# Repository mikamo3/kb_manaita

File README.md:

# kb_manaita
Self made 40% keyboard

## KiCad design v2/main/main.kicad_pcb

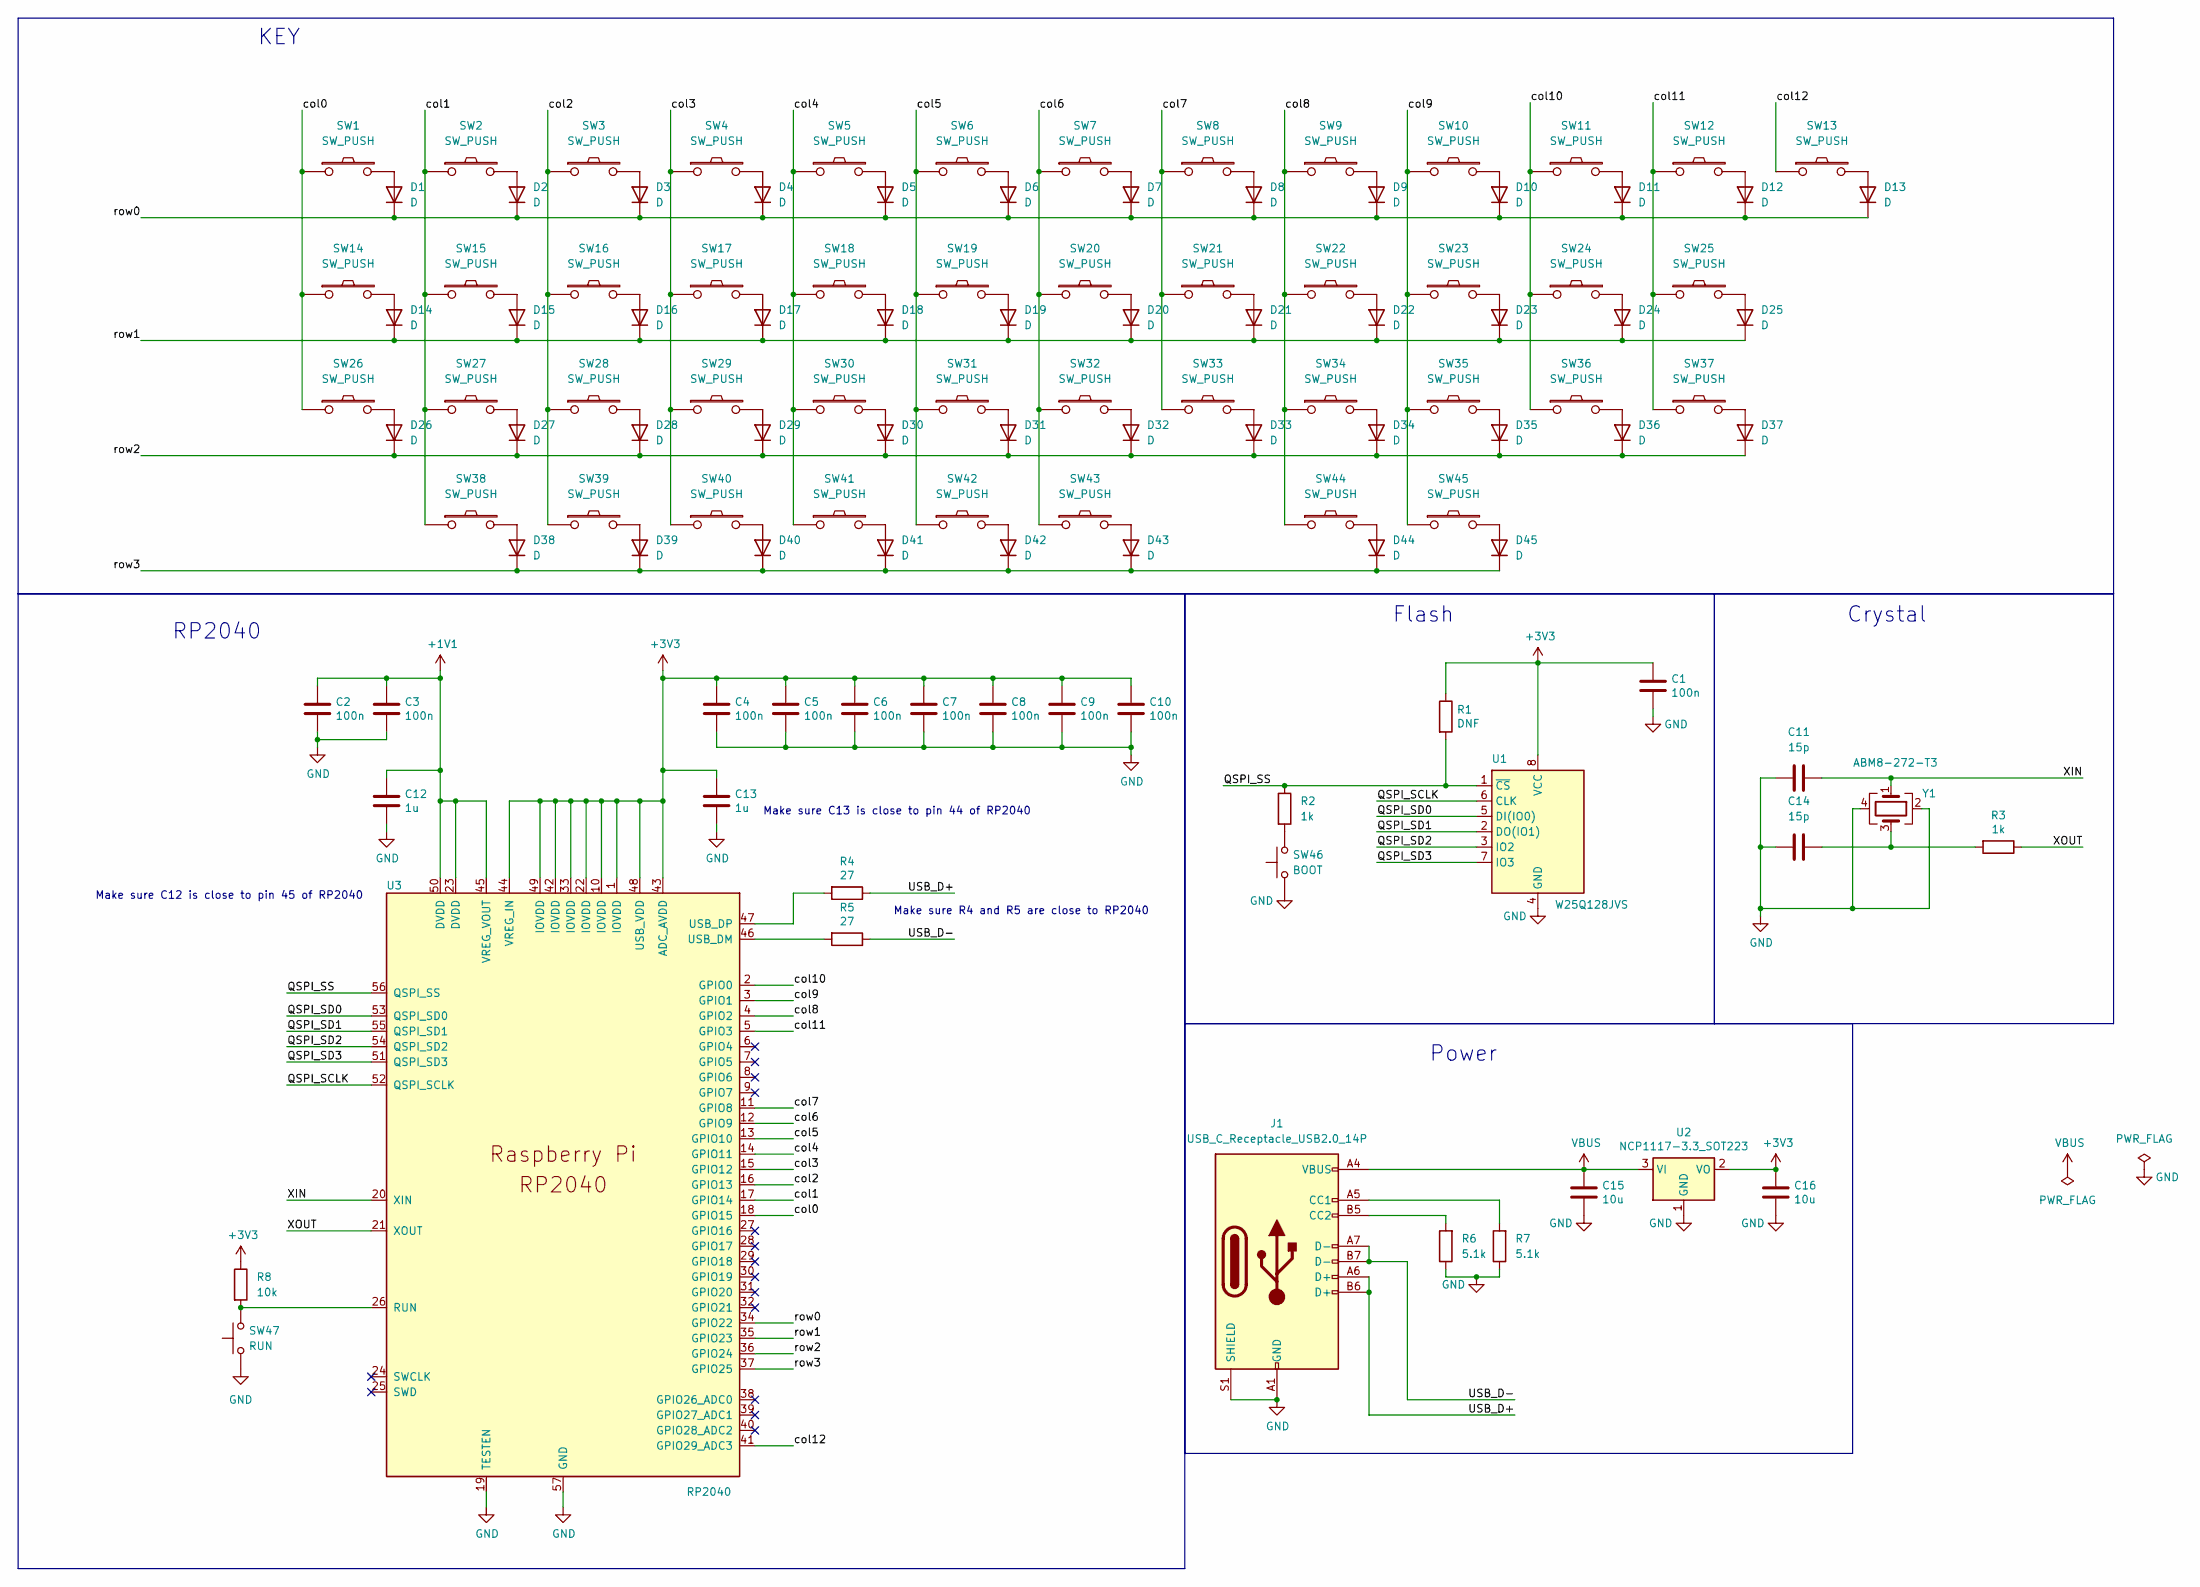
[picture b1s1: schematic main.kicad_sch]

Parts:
C1, C2, C3, C4, C5, C6, C7, C8, C9, C10: 100n; C_0402_1005Metric; LCSC C307331
C11, C14: 15p; C_0603_1608Metric; LCSC C1548
C12, C13: 1u; C_0402_1005Metric; LCSC C52923
C15, C16: 10u; C_0805_2012Metric; LCSC C15850
D1, D2, D3, D4, D5, D6, D7, D8, D9, D10, D11, D12, D13, D14, D15, D16, D17, D18, D19, D20, D21, D22, D23, D24, D25, D26, D27, D28, D29, D30, D31, D32, D33, D34, D35, D36, D37, D38, D39, D40, D41, D42, D43, D44, D45: D; Diode_SOD123; LCSC C8598
J1: USB_C_Receptacle_USB2.0_14P; USB_C_Receptacle_Palconn_UTC16-G; LCSC C2988369
R1: DNF; R_0402_1005Metric
R2, R3: 1k; R_0402_1005Metric; LCSC C11702
R4, R5: 27; R_0603_1608Metric; LCSC C25190
R6, R7: 5.1k; R_0402_1005Metric; LCSC C25905
R8: 10k; R_0402_1005Metric; LCSC C25744
SW1, SW2, SW3, SW4, SW5, SW6, SW7, SW8, SW9, SW10, SW11, SW12, SW13, SW15, SW16, SW17, SW18, SW19, SW20, SW21, SW22, SW23, SW24, SW27, SW28, SW29, SW30, SW31, SW32, SW33, SW34, SW35, SW36, SW41, SW42: SW_PUSH; SW_CherryMX_Hotswap_1.00u
SW14, SW37, SW38, SW39, SW40, SW43, SW44, SW45: SW_PUSH; SW_CherryMX_Hotswap_1.25u
SW25, SW26: SW_PUSH; SW_CherryMX_Hotswap_1.75u
SW46: BOOT; Tact_Switch_5.1_5.1mm_SMD; LCSC C318884
SW47: RUN; Tact_Switch_5.1_5.1mm_SMD; LCSC C318884
U1: W25Q128JVS; SOIC-8_5.23x5.23mm_P1.27mm; LCSC C97521
U2: NCP1117-3.3_SOT223; SOT-223-3_TabPin2; LCSC C6186
U3: RP2040; RP2040-QFN-56; LCSC C2040
Y1: ABM8-272-T3; Crystal_SMD_3225-4Pin_3.2x2.5mm; LCSC C9002

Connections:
+1V1: C2.1, C3.1, C12.1, U3.23 (DVDD), U3.45 (VREG_VOUT), U3.50 (DVDD)
+3V3: C1.1, C4.1, C5.1, C6.1, C7.1, C8.1, C9.1, C10.1, C13.1, C16.1, R1.1, R8.1, U1.8 (VCC), U2.2 (VO), U3.1 (IOVDD), U3.10 (IOVDD), U3.22 (IOVDD), U3.33 (IOVDD), U3.42 (IOVDD), U3.43 (ADC_AVDD), U3.44 (VREG_IN), U3.48 (USB_VDD), U3.49 (IOVDD)
/QSPI_SCLK: U1.6 (CLK), U3.52 (QSPI_SCLK)
/QSPI_SD0: U1.5 (DI(IO0)), U3.53 (QSPI_SD0)
/QSPI_SD1: U1.2 (DO(IO1)), U3.55 (QSPI_SD1)
/QSPI_SD2: U1.3 (IO2), U3.54 (QSPI_SD2)
/QSPI_SD3: U1.7 (IO3), U3.51 (QSPI_SD3)
/QSPI_SS: R1.2, R2.1, U1.1 (~CS), U3.56 (QSPI_SS)
/USB_D+: J1.A6 (D+), J1.B6 (D+), R4.1
/USB_D-: J1.A7 (D-), J1.B7 (D-), R5.1
/XIN: C11.2, U3.20 (XIN), Y1.1
/XOUT: R3.1, U3.21 (XOUT)
/col0: SW1.1, SW14.1, SW26.1, U3.18 (GPIO15)
/col1: SW2.1, SW15.1, SW27.1, SW38.1, U3.17 (GPIO14)
/col2: SW3.1, SW16.1, SW28.1, SW39.1, U3.16 (GPIO13)
/col3: SW4.1, SW17.1, SW29.1, SW40.1, U3.15 (GPIO12)
/col4: SW5.1, SW18.1, SW30.1, SW41.1, U3.14 (GPIO11)
/col5: SW6.1, SW19.1, SW31.1, SW42.1, U3.13 (GPIO10)
/col6: SW7.1, SW20.1, SW32.1, SW43.1, U3.12 (GPIO9)
/col7: SW8.1, SW21.1, SW33.1, U3.11 (GPIO8)
/col8: SW9.1, SW22.1, SW34.1, SW44.1, U3.4 (GPIO2)
/col9: SW10.1, SW23.1, SW35.1, SW45.1, U3.3 (GPIO1)
/col10: SW11.1, SW24.1, SW36.1, U3.2 (GPIO0)
/col11: SW12.1, SW25.1, SW37.1, U3.5 (GPIO3)
/col12: SW13.1, U3.41 (GPIO29_ADC3)
/row0: D1.1 (K), D2.1 (K), D3.1 (K), D4.1 (K), D5.1 (K), D6.1 (K), D7.1 (K), D8.1 (K), D9.1 (K), D10.1 (K), D11.1 (K), D12.1 (K), D13.1 (K), U3.34 (GPIO22)
/row1: D14.1 (K), D15.1 (K), D16.1 (K), D17.1 (K), D18.1 (K), D19.1 (K), D20.1 (K), D21.1 (K), D22.1 (K), D23.1 (K), D24.1 (K), D25.1 (K), U3.35 (GPIO23)
/row2: D26.1 (K), D27.1 (K), D28.1 (K), D29.1 (K), D30.1 (K), D31.1 (K), D32.1 (K), D33.1 (K), D34.1 (K), D35.1 (K), D36.1 (K), D37.1 (K), U3.36 (GPIO24)
/row3: D38.1 (K), D39.1 (K), D40.1 (K), D41.1 (K), D42.1 (K), D43.1 (K), D44.1 (K), D45.1 (K), U3.37 (GPIO25)
GND: C1.2, C2.2, C3.2, C4.2, C5.2, C6.2, C7.2, C8.2, C9.2, C10.2, C11.1, C12.2, C13.2, C14.1, C15.2, C16.2, J1.A1 (GND), J1.A12 (GND), J1.B1 (GND), J1.B12 (GND), J1.S1 (SHIELD), R6.1, R7.1, SW46.1, SW46.2, SW47.1, SW47.2, U1.4 (GND), U2.1 (GND), U3.19 (TESTEN), U3.57 (GND), Y1.2, Y1.4
unnamed: C14.2, R3.2, Y1.3
unnamed: D1.2 (A), SW1.2
unnamed: D2.2 (A), SW2.2
unnamed: D3.2 (A), SW3.2
unnamed: D4.2 (A), SW4.2
unnamed: D5.2 (A), SW5.2
unnamed: D6.2 (A), SW6.2
unnamed: D7.2 (A), SW7.2
unnamed: D8.2 (A), SW8.2
unnamed: D9.2 (A), SW9.2
unnamed: D10.2 (A), SW10.2
unnamed: D11.2 (A), SW11.2
unnamed: D12.2 (A), SW12.2
unnamed: D13.2 (A), SW13.2
unnamed: D14.2 (A), SW14.2
unnamed: D15.2 (A), SW15.2
unnamed: D16.2 (A), SW16.2
unnamed: D17.2 (A), SW17.2
unnamed: D18.2 (A), SW18.2
unnamed: D19.2 (A), SW19.2
unnamed: D20.2 (A), SW20.2
unnamed: D21.2 (A), SW21.2
unnamed: D22.2 (A), SW22.2
unnamed: D23.2 (A), SW23.2
unnamed: D24.2 (A), SW24.2
unnamed: D25.2 (A), SW25.2
unnamed: D26.2 (A), SW26.2
unnamed: D27.2 (A), SW27.2
unnamed: D28.2 (A), SW28.2
unnamed: D29.2 (A), SW29.2
unnamed: D30.2 (A), SW30.2
unnamed: D31.2 (A), SW31.2
unnamed: D32.2 (A), SW32.2
unnamed: D33.2 (A), SW33.2
unnamed: D34.2 (A), SW34.2
unnamed: D35.2 (A), SW35.2
unnamed: D36.2 (A), SW36.2
unnamed: D37.2 (A), SW37.2
unnamed: D38.2 (A), SW38.2
unnamed: D39.2 (A), SW39.2
unnamed: D40.2 (A), SW40.2
unnamed: D41.2 (A), SW41.2
unnamed: D42.2 (A), SW42.2
unnamed: D43.2 (A), SW43.2
unnamed: D44.2 (A), SW44.2
unnamed: D45.2 (A), SW45.2
unnamed: J1.A5 (CC1), R7.2
unnamed: J1.B5 (CC2), R6.2
unnamed: R2.2, SW46.3, SW46.4
unnamed: R8.2, SW47.3, SW47.4, U3.26 (RUN)
unnamed: R5.2, U3.46 (USB_DM)
unnamed: R4.2, U3.47 (USB_DP)
VBUS: C15.1, J1.A4 (VBUS), J1.A9 (VBUS), J1.B4 (VBUS), J1.B9 (VBUS), U2.3 (VI)

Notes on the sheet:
KEY
RP2040
Make sure R4 and R5 are close to RP2040
Power
Flash
Crystal
Make sure C12 is close to pin 45 of RP2040
Make sure C13 is close to pin 44 of RP2040

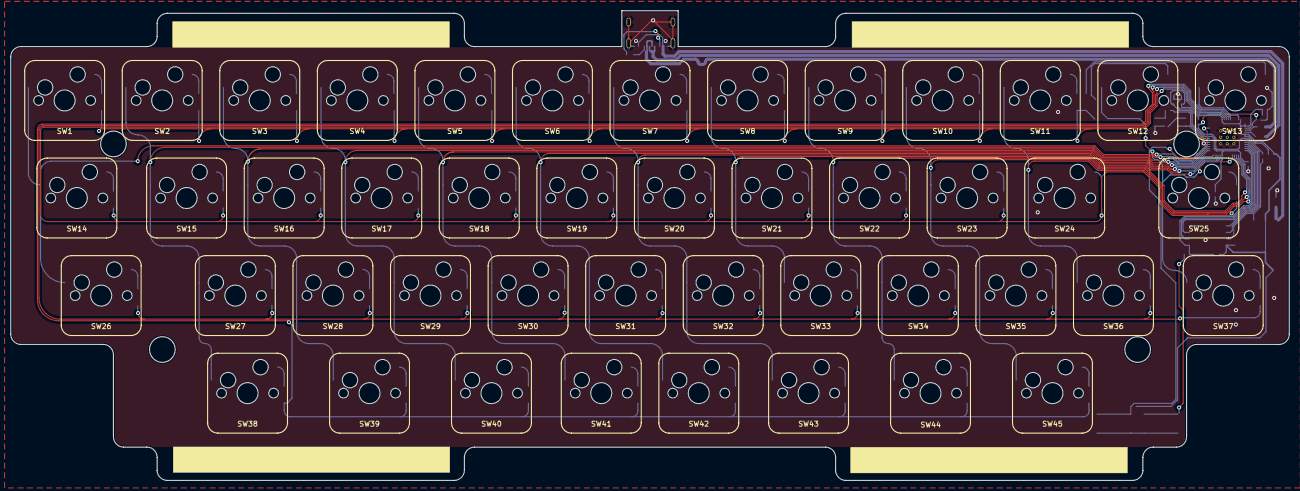
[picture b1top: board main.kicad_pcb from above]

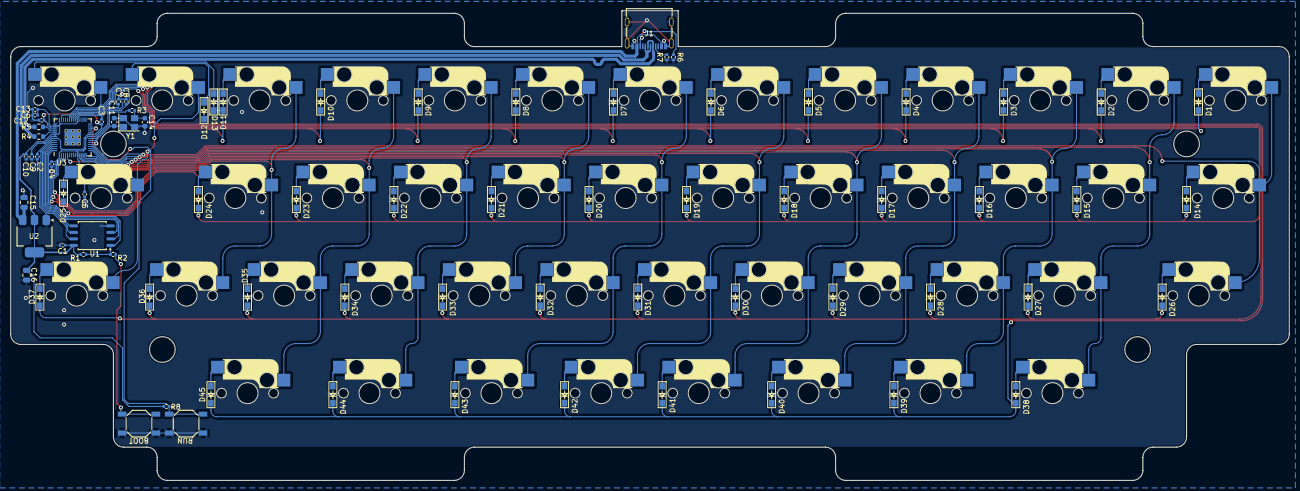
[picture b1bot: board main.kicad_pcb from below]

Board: 2 copper layers, 249.6 x 91.7 mm, 121 parts (76 on the bottom side), 83 nets.

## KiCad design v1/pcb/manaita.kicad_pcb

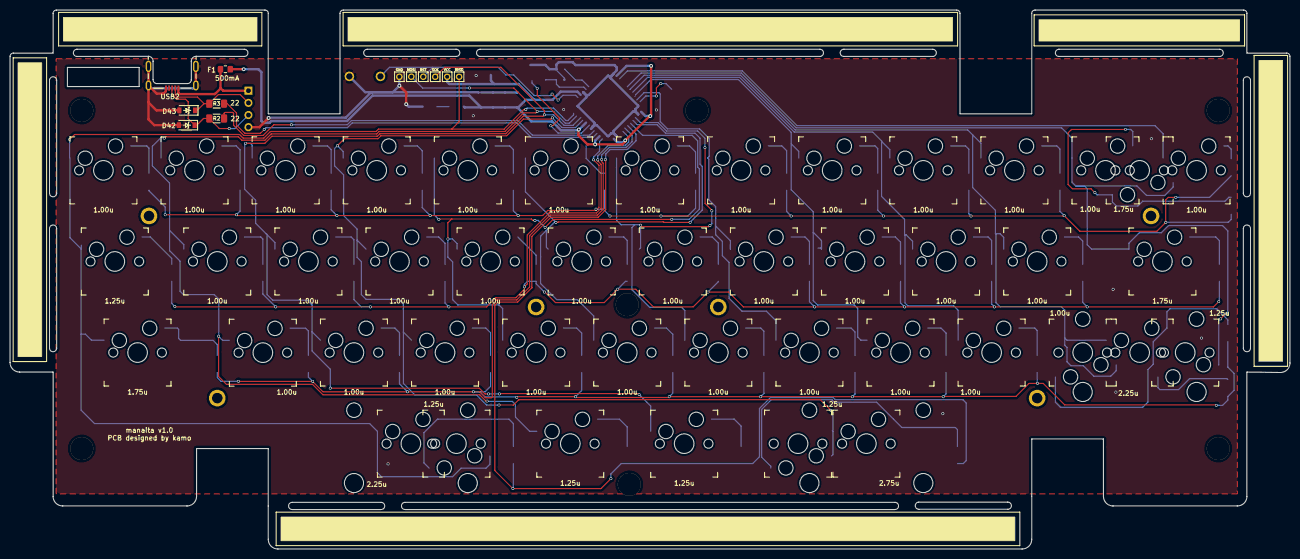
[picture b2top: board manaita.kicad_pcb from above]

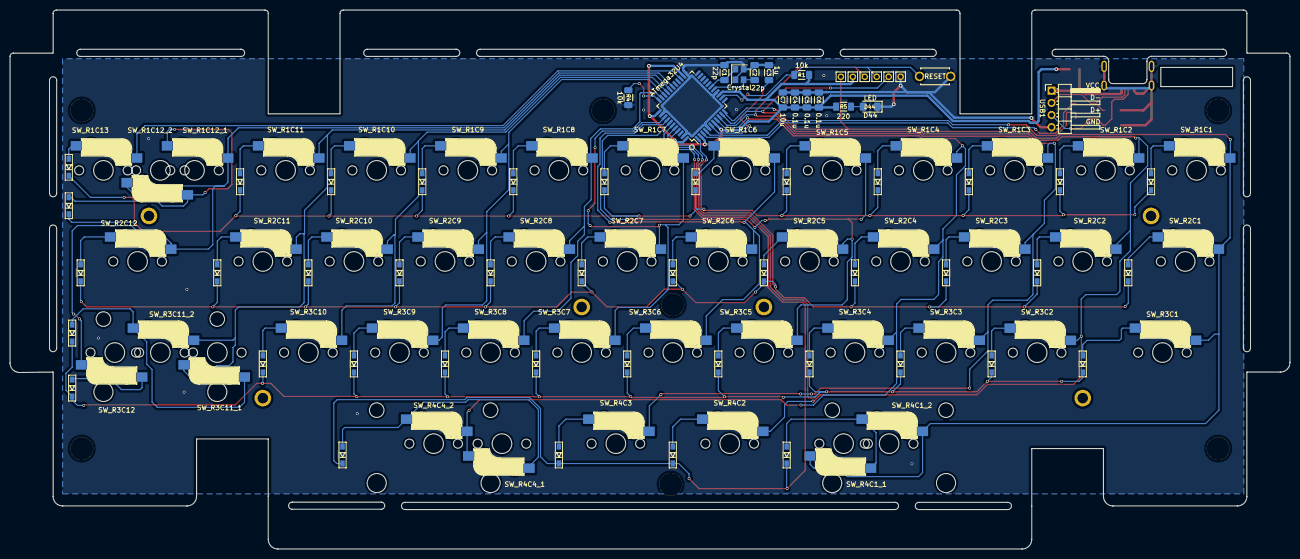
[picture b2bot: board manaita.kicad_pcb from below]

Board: 2 copper layers, 267.7 x 112.7 mm, 126 parts (56 on the bottom side), 71 nets.

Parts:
C1, C2: 22p; C_1206_3216Metric_Pad1.33x1.80mm_HandSolder
C3: 1u; C_1206_3216Metric_Pad1.33x1.80mm_HandSolder
C4, C5, C6: 0.1u; C_1206_3216Metric_Pad1.33x1.80mm_HandSolder
C7: 10u; C_1206_3216Metric_Pad1.33x1.80mm_HandSolder
D1, D2, D3, D4, D5, D6, D7, D8, D9, D10, D11, D12, D13, D14, D15, D16, D17, D18, D19, D20, D21, D22, D23, D24, D25, D26, D27, D28, D29, D30, D31, D32, D33, D34, D35, D36, D37, D38, D39, D40, D41: D; D3_SMD_1side
D42, D43: D_Zener; D_SOD-123-Zener
D44: LED; LED_1206_3216Metric_Pad1.42x1.75mm_HandSolder
F1: 500mA; Fuse_0805_2012Metric_Pad1.15x1.40mm_HandSolder
J1: SCK; 1pin_conn
J2: RST; 1pin_conn
J3: MOSI; 1pin_conn
J4: MISO; 1pin_conn
J5: VCC; 1pin_conn
J6: GND; 1pin_conn
JH1, JH2, JH3, JH4, JH5, JH6: Conn_01x01; M2hole
R1, R4: 10k; R_1206_3216Metric_Pad1.30x1.75mm_HandSolder
R2, R3: 22; R_1206_3216Metric_Pad1.30x1.75mm_HandSolder
R5: 220; R_1206_3216Metric_Pad1.30x1.75mm_HandSolder
RefH1, RefH1#2, RefH1#3, RefH1#4, RefH1#5, RefH1#6, RefH3: Val**; SpacerHole
SW_R1C1, SW_R1C2, SW_R1C3, SW_R1C4, SW_R1C5, SW_R1C6, SW_R1C7, SW_R1C8, SW_R1C9, SW_R1C10, SW_R1C11, SW_R1C12_1, SW_R1C13, SW_R2C2, SW_R2C3, SW_R2C4, SW_R2C5, SW_R2C6, SW_R2C7, SW_R2C8, SW_R2C9, SW_R2C10, SW_R2C11, SW_R3C2, SW_R3C3, SW_R3C4, SW_R3C5, SW_R3C6, SW_R3C7, SW_R3C8, SW_R3C9, SW_R3C10, SW_R3C11_1: SW_PUSH; CherryMX_Hotswap_1.00u_1side
SW_R1C12_2, SW_R2C12, SW_R3C1: SW_PUSH; CherryMX_Hotswap_1.75u_1side
SW_R2C1, SW_R3C12, SW_R4C1_1, SW_R4C2, SW_R4C3, SW_R4C4_1: SW_PUSH; CherryMX_Hotswap_1.25u_1side
SW_R3C11_2, SW_R4C1_2: SW_PUSH; CherryMX_Hotswap_2.25u_1side
SW_R4C4_2: SW_PUSH; CherryMX_Hotswap_2.75u_1side
SW_RESET1: SW_Push; ResetSW_1side
U1: ATmega32U4; TQFP-44_10x10mm_P0.8mm
USB1: Conn_01x04; PinHeader_1x04_P2.54mm_Horizontal
USB2: molex_47642-0001; 47642-0001_HandSoldering
Y1: Crystal; Crystal_SMD_3225-4pin_3.2x2.5mm

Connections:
+5V: C4.1, C5.1, C6.1, C7.1, F1.2, J5.1, R1.2, R5.2, U1.2, U1.7, U1.14, U1.24, U1.34, U1.44
D+: D42.1, R2.2, USB1.3, USB2.3
D-: D43.1, R3.2, USB1.2, USB2.2
GND: C1.2, C2.2, C3.2, C4.2, C5.2, C6.2, C7.2, D42.2, D43.2, D44.1, J6.1, R4.1, SW_RESET1.1, U1.5, U1.15, U1.23, U1.35, U1.43, USB1.4, USB2.5, USB2.6, Y1.2, Y1.4
unnamed: C1.1, U1.17, Y1.1
unnamed: C2.1, U1.16, Y1.3
unnamed: C3.1, U1.6
unnamed: D1.2, SW_R1C1.2
unnamed: D2.2, SW_R1C2.2
unnamed: D3.2, SW_R1C3.2
unnamed: D4.2, SW_R1C4.2
unnamed: D5.2, SW_R1C5.2
unnamed: D6.2, SW_R1C6.2
unnamed: D7.2, SW_R1C7.2
unnamed: D8.2, SW_R1C8.2
unnamed: D9.2, SW_R1C9.2
unnamed: D10.2, SW_R1C10.2
unnamed: D11.2, SW_R1C11.2
unnamed: D12.2, SW_R1C12_1.2, SW_R1C12_2.2
unnamed: D13.2, SW_R1C13.2
unnamed: D14.2, SW_R2C1.2
unnamed: D15.2, SW_R2C2.2
unnamed: D16.2, SW_R2C3.2
unnamed: D17.2, SW_R2C4.2
unnamed: D18.2, SW_R2C5.2
unnamed: D19.2, SW_R2C6.2
unnamed: D20.2, SW_R2C7.2
unnamed: D21.2, SW_R2C8.2
unnamed: D22.2, SW_R2C9.2
unnamed: D23.2, SW_R2C10.2
unnamed: D24.2, SW_R2C11.2
unnamed: D25.2, SW_R2C12.2
unnamed: D26.2, SW_R3C1.2
unnamed: D27.2, SW_R3C2.2
unnamed: D28.2, SW_R3C3.2
unnamed: D29.2, SW_R3C4.2
unnamed: D30.2, SW_R3C5.2
unnamed: D31.2, SW_R3C6.2
unnamed: D32.2, SW_R3C7.2
unnamed: D33.2, SW_R3C8.2
unnamed: D34.2, SW_R3C9.2
unnamed: D35.2, SW_R3C10.2
unnamed: D36.2, SW_R3C11_1.2, SW_R3C11_2.2
unnamed: D37.2, SW_R3C12.2
unnamed: D38.2, SW_R4C1_1.2, SW_R4C1_2.2
unnamed: D39.2, SW_R4C2.2
unnamed: D40.2, SW_R4C3.2
unnamed: D41.2, SW_R4C4_1.2, SW_R4C4_2.2
unnamed: D44.2, R5.1
unnamed: J2.1, R1.1, SW_RESET1.2, U1.13
unnamed: R2.1, U1.4
unnamed: R3.1, U1.3
unnamed: R4.2, U1.33
VCC: F1.1, USB1.1, USB2.1
col0: J4.1, SW_R1C1.1, SW_R2C1.1, SW_R3C1.1, SW_R4C1_1.1, SW_R4C1_2.1, U1.11
col1: J3.1, SW_R1C2.1, SW_R2C2.1, SW_R3C2.1, SW_R4C2.1, U1.10
col2: J1.1, SW_R1C3.1, SW_R2C3.1, SW_R3C3.1, SW_R4C3.1, U1.9
col3: SW_R1C4.1, SW_R2C4.1, SW_R3C4.1, SW_R4C4_1.1, SW_R4C4_2.1, U1.8
col4: SW_R1C5.1, SW_R2C5.1, SW_R3C5.1, U1.38
col5: SW_R1C6.1, SW_R2C6.1, SW_R3C6.1, U1.37
col6: SW_R1C7.1, SW_R2C7.1, SW_R3C7.1, U1.36
col7: SW_R1C8.1, SW_R2C8.1, SW_R3C8.1, U1.32
col8: SW_R1C9.1, SW_R2C9.1, SW_R3C9.1, U1.31
col9: SW_R1C10.1, SW_R2C10.1, SW_R3C10.1, U1.30
col10: SW_R1C11.1, SW_R2C11.1, SW_R3C11_1.1, SW_R3C11_2.1, U1.29
col11: SW_R1C12_1.1, SW_R1C12_2.1, SW_R2C12.1, SW_R3C12.1, U1.28
col12: SW_R1C13.1, U1.25
row0: D1.1, D2.1, D3.1, D4.1, D5.1, D6.1, D7.1, D8.1, D9.1, D10.1, D11.1, D12.1, D13.1, U1.1
row1: D14.1, D15.1, D16.1, D17.1, D18.1, D19.1, D20.1, D21.1, D22.1, D23.1, D24.1, D25.1, U1.41
row2: D26.1, D27.1, D28.1, D29.1, D30.1, D31.1, D32.1, D33.1, D34.1, D35.1, D36.1, D37.1, U1.40
row3: D38.1, D39.1, D40.1, D41.1, U1.39

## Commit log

2020-11-15 add keyboard layout
2020-11-19 create pcb
2020-11-21 :bug: (keyboard layout) fix keycap size
2020-11-21 :bug: (sch) fix switch
2020-11-21 :sparkles: (pcb) add pcb
2020-12-02 :construction: (all) WIP
2020-12-05 create pcb done
2020-12-07 :sparkles: (pcb) fix chore
2020-12-09 :sparkles: (all) add plate and fix pcb
2020-12-13 :heavy_plus_sign: (gerber_rename) add gerber_rename
2020-12-13 :heavy_plus_sign: (footprint) add digikey-kicad-library
2020-12-13 :sparkles: (all) last fix before create pcb
2020-12-13 :sparkles: (pcb) add bottomplate silk
2023-06-17 :sparkles: (pcb) add
2024-08-26 move exist contents to v1
2025-05-27 Add initial KiCad project files for version 2
    - Created top.kicad_pro with board design settings, rules, and dimensions.
    - Added top.kicad_sch with basic schematic structure and metadata.
2025-06-07 update module
